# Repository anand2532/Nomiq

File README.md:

# Nomiq — Standalone LoRa Voice, Text & Photo Messenger

Nomiq is a pocket-sized, battery-powered messenger that sends **voice notes, offline speech-to-text messages and photographs** directly between devices over **LoRa** — no phone, no internet, no cellular, no cloud.

| | |
|---|---|
| **Main MCU** | ESP32-S3 (16 MB flash / 8 MB PSRAM) |
| **Radio** | Semtech SX1262, 865–867 MHz (India), 125 kHz BW |
| **Speech-to-text** | Offline — power-gated Linux co-processor (see [ADR-0002](docs/adr/0002-offline-speech-recognition-architecture.md)) |
| **Audio** | I²S MEMS mic, I²S class-D amp + speaker, Codec2 1200/2400 bps |
| **Camera** | OV2640 (DVP), on-chip JPEG |
| **Display** | 2.4–2.8" SPI TFT, 320×240 |
| **Storage** | microSD |
| **Power** | 1S Li-ion 3000 mAh, USB-C charging, fuel gauge |
| **Enclosure** | ~130 × 70 × 30 mm, 3D-printed (build123d, parametric) |
| **EDA** | KiCad 9/10, 4-layer |

## Repository map

```
docs/                    Requirements, architecture, specs, ADRs, roadmap
  00-requirements.md       Traceable requirements (REQ-xxx) from the product brief
  01-system-architecture.md
  02-hardware-architecture.md   Block diagram, pin map, power tree
  03-development-roadmap.md     Phases, gates, deliverables
  specs/                   Protocol, link budget, power budget, STT, UI, storage
  adr/                     Architecture Decision Records
hardware/
  kicad/nomiq/             KiCad project (schematic + PCB)
  bom/                     BOM and component selection
  bringup/                 Board bring-up checklist
mechanical/
  enclosure/               Parametric enclosure (build123d)
  exports/                 Generated STEP / STL (CI artefacts)
firmware/                  ESP-IDF project; protocol core is host-testable C
tools/                     Calculators (LoRa airtime, power budget)
tests/                     Test plans and reports
.claude/agents/            Engineering agent "bots" (one per discipline)
.mcp.json                  MCP servers: KiCad + CAD
```

## Getting started

```bash
# LoRa airtime / transfer-time table (India-compliant presets)
python3 tools/lora_airtime.py --table

# Host unit tests for the protocol core (no hardware needed)
make -C firmware/components/nomiq_proto/test

# Build the enclosure (needs: pip install build123d)
python3 mechanical/enclosure/enclosure.py --out mechanical/exports
```

Working with Claude Code and the engineering agents: see [docs/ai-workflow.md](docs/ai-workflow.md).

## Status

Phase 0 — architecture & de-risking. Original brief: [project.txt](project.txt). See [docs/03-development-roadmap.md](docs/03-development-roadmap.md).

**Gating risks (must close before PCB freeze):**
1. Offline STT on target hardware (Phase 3 benchmark) — ESP32-S3 alone cannot do free-form dictation.
2. Indian regulatory profile (duty-cycle / ERP) — drives photo/voice transfer times. See [lora-link-budget](docs/specs/lora-link-budget.md).
3. ESP32-S3 GPIO budget with camera + display + LoRa + SD + I²S — see pin map.

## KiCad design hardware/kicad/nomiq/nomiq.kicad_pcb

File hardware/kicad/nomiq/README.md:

# KiCad project — Nomiq main board

Open `nomiq.kicad_pro` in KiCad 8 or newer. The schematic is **generated** from the netlist source of truth
`hardware/design/nomiq_hw.py` by `hardware/design/gen_kicad.py`:

```
python3 hardware/design/gen_kicad.py          # regenerate nomiq.kicad_sch, 01..08 sheets, lib/nomiq.kicad_sym
python3 hardware/design/gen_kicad.py --check  # rebuild connectivity from the generated S-expressions and compare with nomiq_hw.py (runs in make tools / CI)
kicad-cli sch erc nomiq.kicad_sch             # ERC on a machine with KiCad
```

Structure: root sheet with 8 hierarchical sheets (power, MCU, radio, audio, camera, display+storage, UI, STT).
Every pin is connected by a short wire to a global label carrying the net name, so connectivity is exact and
the sheets are readable; unused pins carry no-connect flags. Edit `nomiq_hw.py`, not the `.kicad_sch` files.

Pad numbers: U1 (ESP32-S3-WROOM-1) and U2 (SX1262 QFN-24) follow the datasheets. 32 parts still use
placeholder pad numbers (marked `unverified` in `gen_kicad.py`) — verify against datasheets and assign
footprints before PCB layout (electronics-schematic-engineer, gate G2).

- Project libraries: `lib/nomiq.kicad_sym` (generated), `lib/nomiq.pretty` (registered in sym-lib-table / fp-lib-table)
- PCB: create `nomiq.kicad_pcb` from the PCB editor (Update PCB from schematic); outline from `mechanical/enclosure/params.py`
- Fabrication outputs: `fab/` (Gerbers, drill, CPL, BOM) — release via tag `hw-vX.Y`
- MCP: `.mcp.json` points kicad-mcp-pro at this folder (`KICAD_MCP_PROJECT_DIR`)

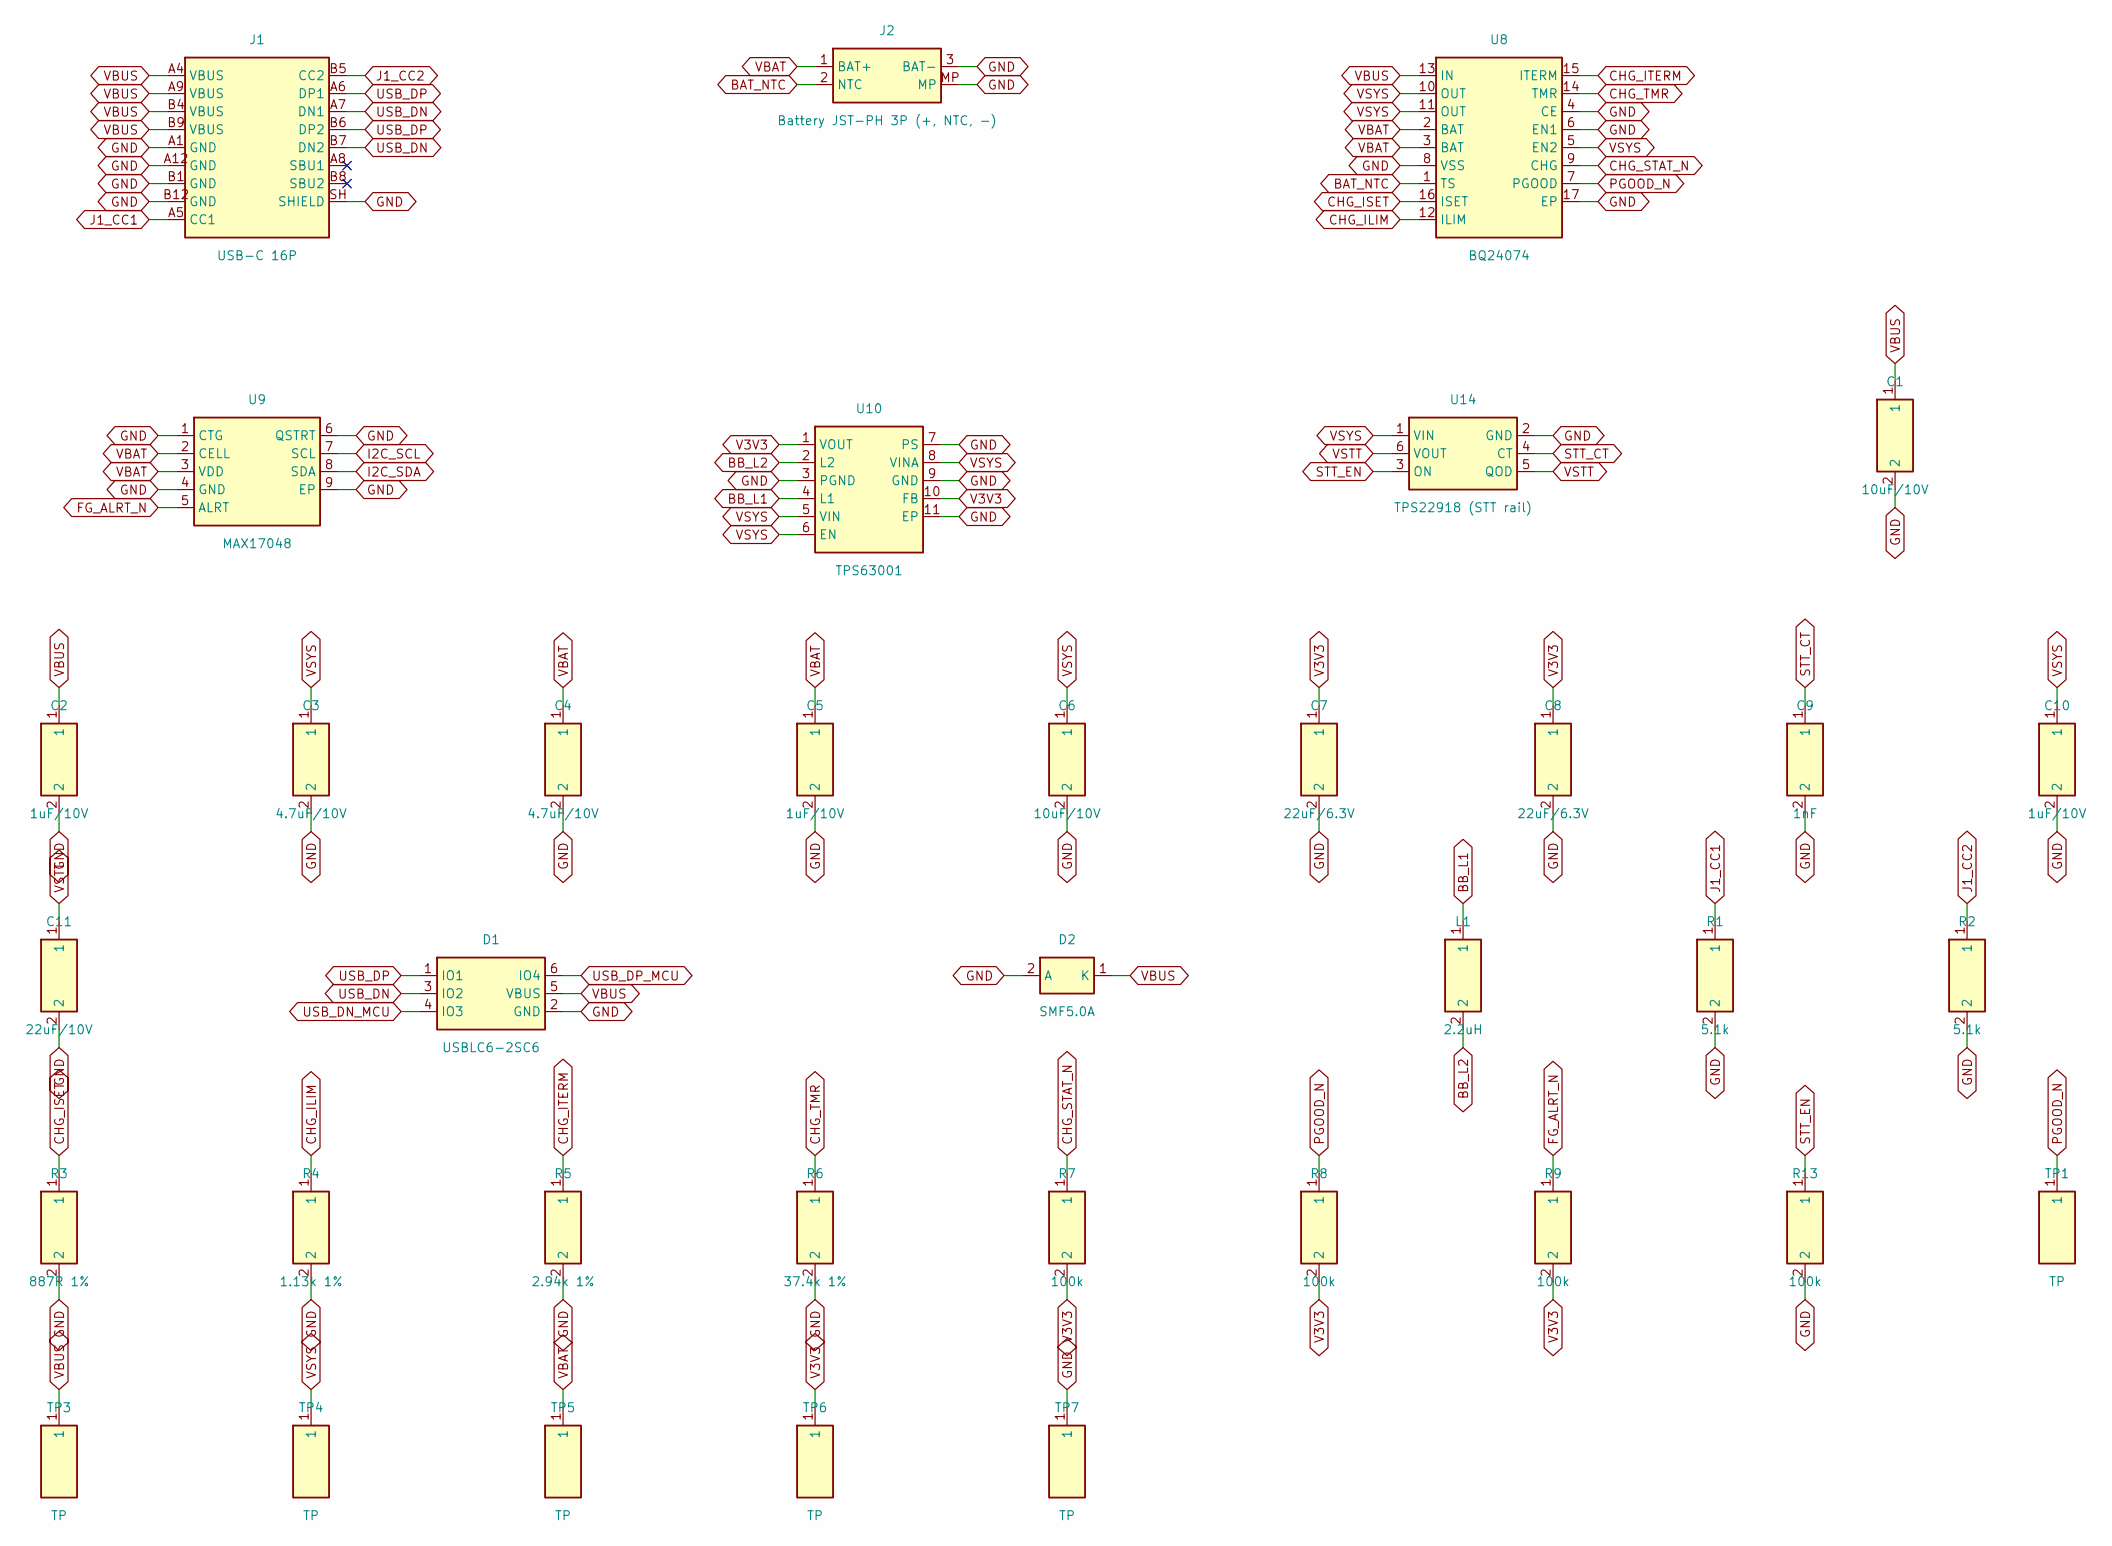
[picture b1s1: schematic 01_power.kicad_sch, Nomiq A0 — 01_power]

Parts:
C1, C6: 10uF/10V; C_0603_1608Metric
C2, C5, C10: 1uF/10V; C_0402_1005Metric
C3, C4: 4.7uF/10V; C_0603_1608Metric
C7, C8: 22uF/6.3V; C_0805_2012Metric
C9: 1nF; C_0402_1005Metric
C11: 22uF/10V; C_0805_2012Metric
D1: USBLC6-2SC6; SOT-23-6; MPN STMicro USBLC6-2SC6
D2: SMF5.0A; D_SOD-123F; MPN Littelfuse SMF5.0A
J1: USB-C 16P; USB_C_Receptacle_GCT_USB4105-xx-A_16P_TopMnt_Horizontal; MPN GCT USB4105-GF-A
J2: Battery JST-PH 3P (+, NTC, -); JST_PH_S3B-PH-SM4-TB_1x03-1MP_P2.00mm_Horizontal; MPN JST S3B-PH-SM4-TB
L1: 2.2uH; L_Taiyo-Yuden_NR-40xx; MPN Taiyo Yuden NRS4018T2R2MDGJ
R1, R2: 5.1k; R_0402_1005Metric
R3: 887R 1%; R_0402_1005Metric
R4: 1.13k 1%; R_0402_1005Metric
R5: 2.94k 1%; R_0402_1005Metric
R6: 37.4k 1%; R_0402_1005Metric
R7, R8, R9, R13: 100k; R_0402_1005Metric
TP1, TP3, TP4, TP5, TP6, TP7: TP; TestPoint_Pad_D1.0mm
U8: BQ24074; VQFN-16-1EP_3x3mm_P0.5mm_EP1.6x1.6mm; MPN TI BQ24074RGTR
U9: MAX17048; TDFN-8-1EP_2x2mm_P0.5mm_EP0.8x1.2mm; MPN Analog Devices MAX17048G+T10
U10: TPS63001; Texas_S-PVSON-N10; MPN TI TPS63001DRCR
U14: TPS22918 (STT rail); SOT-23-6; MPN TI TPS22918DBVR

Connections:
BAT_NTC: J2.2 (NTC), U8.1 (TS)
BB_L1: L1.1, U10.4 (L1)
BB_L2: L1.2, U10.2 (L2)
CHG_ILIM: R4.1, U8.12 (ILIM)
CHG_ISET: R3.1, U8.16 (ISET)
CHG_ITERM: R5.1, U8.15 (ITERM)
CHG_STAT_N: R7.1, U8.9 (CHG); also elsewhere on the board
CHG_TMR: R6.1, U8.14 (TMR)
FG_ALRT_N: R9.1, U9.5 (ALRT); also elsewhere on the board
GND: C1.2, C2.2, C3.2, C4.2, C5.2, C6.2, C7.2, C8.2, C9.2, C10.2, C11.2, D1.2 (GND), D2.2 (A), J1.A1 (GND), J1.A12 (GND), J1.B1 (GND), J1.B12 (GND), J1.SH (SHIELD), J2.3 (BAT-), J2.MP, R1.2, R2.2, R3.2, R4.2, R5.2, R6.2, R13.2, TP7.1, U8.4 (CE), U8.6 (EN1), U8.8 (VSS), U8.17 (EP), U9.1 (CTG), U9.4 (GND), U9.6 (QSTRT), U9.9 (EP), U10.3 (PGND), U10.7 (PS), U10.9 (GND), U10.11 (EP), U14.2 (GND); also elsewhere on the board
I2C_SCL: U9.7 (SCL); also elsewhere on the board
I2C_SDA: U9.8 (SDA); also elsewhere on the board
J1_CC1: J1.A5 (CC1), R1.1
J1_CC2: J1.B5 (CC2), R2.1
PGOOD_N: R8.1, TP1.1, U8.7 (PGOOD)
STT_CT: C9.1, U14.4 (CT)
STT_EN: R13.1, U14.3 (ON); also elsewhere on the board
USB_DN: D1.3 (IO2), J1.A7 (DN1), J1.B7 (DN2)
USB_DN_MCU: D1.4 (IO3); also elsewhere on the board
USB_DP: D1.1 (IO1), J1.A6 (DP1), J1.B6 (DP2)
USB_DP_MCU: D1.6 (IO4); also elsewhere on the board
V3V3: C7.1, C8.1, R7.2, R8.2, R9.2, TP6.1, U10.1 (VOUT), U10.10 (FB); also elsewhere on the board
VBAT: C4.1, C5.1, J2.1 (BAT+), TP5.1, U8.2 (BAT), U8.3 (BAT), U9.2 (CELL), U9.3 (VDD)
VBUS: C1.1, C2.1, D1.5 (VBUS), D2.1 (K), J1.A4 (VBUS), J1.A9 (VBUS), J1.B4 (VBUS), J1.B9 (VBUS), TP3.1, U8.13 (IN)
VSTT: C11.1, U14.5 (QOD), U14.6 (VOUT); also elsewhere on the board
VSYS: C3.1, C6.1, C10.1, TP4.1, U8.5 (EN2), U8.10 (OUT), U8.11 (OUT), U10.5 (VIN), U10.6 (EN), U10.8 (VINA), U14.1 (VIN); also elsewhere on the board

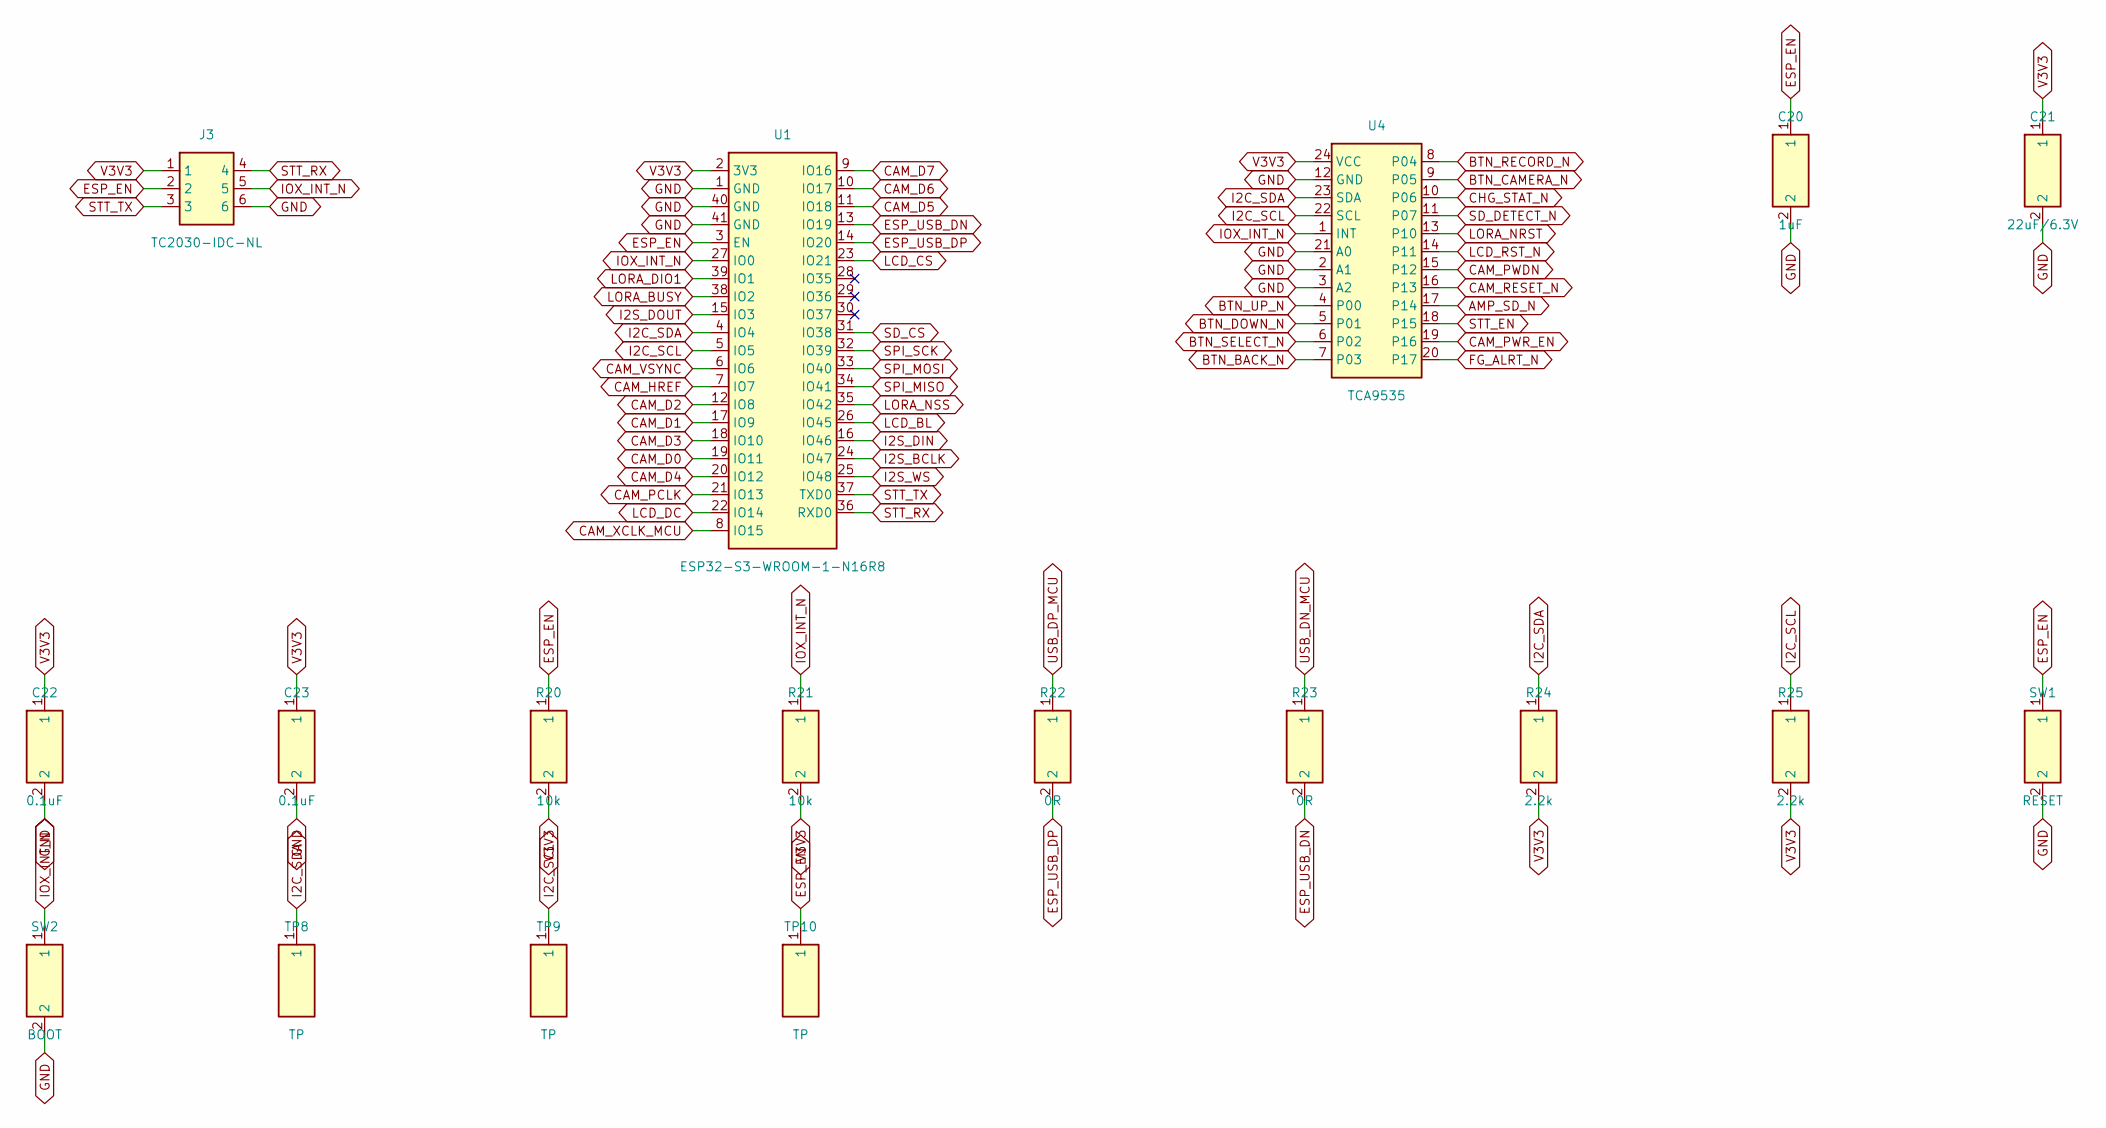
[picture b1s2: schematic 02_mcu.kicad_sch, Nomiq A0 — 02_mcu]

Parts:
C20: 1uF; C_0402_1005Metric
C21: 22uF/6.3V; C_0805_2012Metric
C22, C23: 0.1uF; C_0402_1005Metric
J3: TC2030-IDC-NL; Tag-Connect_TC2030-IDC-NL_2x03_P1.27mm_Vertical; MPN Tag-Connect TC2030-IDC-NL
R20, R21: 10k; R_0402_1005Metric
R22, R23: 0R; R_0402_1005Metric
R24, R25: 2.2k; R_0402_1005Metric
SW1: RESET; SW_SPST_PTS810; MPN C&K PTS810 SJM 250 SMTR LFS
SW2: BOOT; SW_SPST_PTS810; MPN C&K PTS810 SJM 250 SMTR LFS
TP8, TP9, TP10: TP; TestPoint_Pad_D1.0mm
U1: ESP32-S3-WROOM-1-N16R8; ESP32-S3-WROOM-1; MPN Espressif ESP32-S3-WROOM-1-N16R8
U4: TCA9535; TSSOP-24_4.4x7.8mm_P0.65mm; MPN TI TCA9535PWR

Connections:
AMP_SD_N: U4.17 (P14); also elsewhere on the board
BTN_BACK_N: U4.7 (P03); also elsewhere on the board
BTN_CAMERA_N: U4.9 (P05); also elsewhere on the board
BTN_DOWN_N: U4.5 (P01); also elsewhere on the board
BTN_RECORD_N: U4.8 (P04); also elsewhere on the board
BTN_SELECT_N: U4.6 (P02); also elsewhere on the board
BTN_UP_N: U4.4 (P00); also elsewhere on the board
CAM_D0: U1.19 (IO11); also elsewhere on the board
CAM_D1: U1.17 (IO9); also elsewhere on the board
CAM_D2: U1.12 (IO8); also elsewhere on the board
CAM_D3: U1.18 (IO10); also elsewhere on the board
CAM_D4: U1.20 (IO12); also elsewhere on the board
CAM_D5: U1.11 (IO18); also elsewhere on the board
CAM_D6: U1.10 (IO17); also elsewhere on the board
CAM_D7: U1.9 (IO16); also elsewhere on the board
CAM_HREF: U1.7 (IO7); also elsewhere on the board
CAM_PCLK: U1.21 (IO13); also elsewhere on the board
CAM_PWDN: U4.15 (P12); also elsewhere on the board
CAM_PWR_EN: U4.19 (P16); also elsewhere on the board
CAM_RESET_N: U4.16 (P13); also elsewhere on the board
CAM_VSYNC: U1.6 (IO6); also elsewhere on the board
CAM_XCLK_MCU: U1.8 (IO15); also elsewhere on the board
CHG_STAT_N: U4.10 (P06); also elsewhere on the board
ESP_EN: C20.1, J3.2, R20.1, SW1.1, TP10.1, U1.3 (EN); also elsewhere on the board
ESP_USB_DN: R23.2, U1.13 (IO19)
ESP_USB_DP: R22.2, U1.14 (IO20)
FG_ALRT_N: U4.20 (P17); also elsewhere on the board
GND: C20.2, C21.2, C22.2, C23.2, J3.6, SW1.2, SW2.2, U1.1 (GND), U1.40 (GND), U1.41 (GND), U4.2 (A1), U4.3 (A2), U4.12 (GND), U4.21 (A0); also elsewhere on the board
I2C_SCL: R25.1, TP9.1, U1.5 (IO5), U4.22 (SCL); also elsewhere on the board
I2C_SDA: R24.1, TP8.1, U1.4 (IO4), U4.23 (SDA); also elsewhere on the board
I2S_BCLK: U1.24 (IO47); also elsewhere on the board
I2S_DIN: U1.16 (IO46); also elsewhere on the board
I2S_DOUT: U1.15 (IO3); also elsewhere on the board
I2S_WS: U1.25 (IO48); also elsewhere on the board
IOX_INT_N: J3.5, R21.1, SW2.1, U1.27 (IO0), U4.1 (INT)
LCD_BL: U1.26 (IO45); also elsewhere on the board
LCD_CS: U1.23 (IO21); also elsewhere on the board
LCD_DC: U1.22 (IO14); also elsewhere on the board
LCD_RST_N: U4.14 (P11); also elsewhere on the board
LORA_BUSY: U1.38 (IO2); also elsewhere on the board
LORA_DIO1: U1.39 (IO1); also elsewhere on the board
LORA_NRST: U4.13 (P10); also elsewhere on the board
LORA_NSS: U1.35 (IO42); also elsewhere on the board
SD_CS: U1.31 (IO38); also elsewhere on the board
SD_DETECT_N: U4.11 (P07); also elsewhere on the board
SPI_MISO: U1.34 (IO41); also elsewhere on the board
SPI_MOSI: U1.33 (IO40); also elsewhere on the board
SPI_SCK: U1.32 (IO39); also elsewhere on the board
STT_EN: U4.18 (P15); also elsewhere on the board
STT_RX: J3.4, U1.36 (RXD0); also elsewhere on the board
STT_TX: J3.3, U1.37 (TXD0); also elsewhere on the board
USB_DN_MCU: R23.1; also elsewhere on the board
USB_DP_MCU: R22.1; also elsewhere on the board
V3V3: C21.1, C22.1, C23.1, J3.1, R20.2, R21.2, R24.2, R25.2, U1.2 (3V3), U4.24 (VCC); also elsewhere on the board

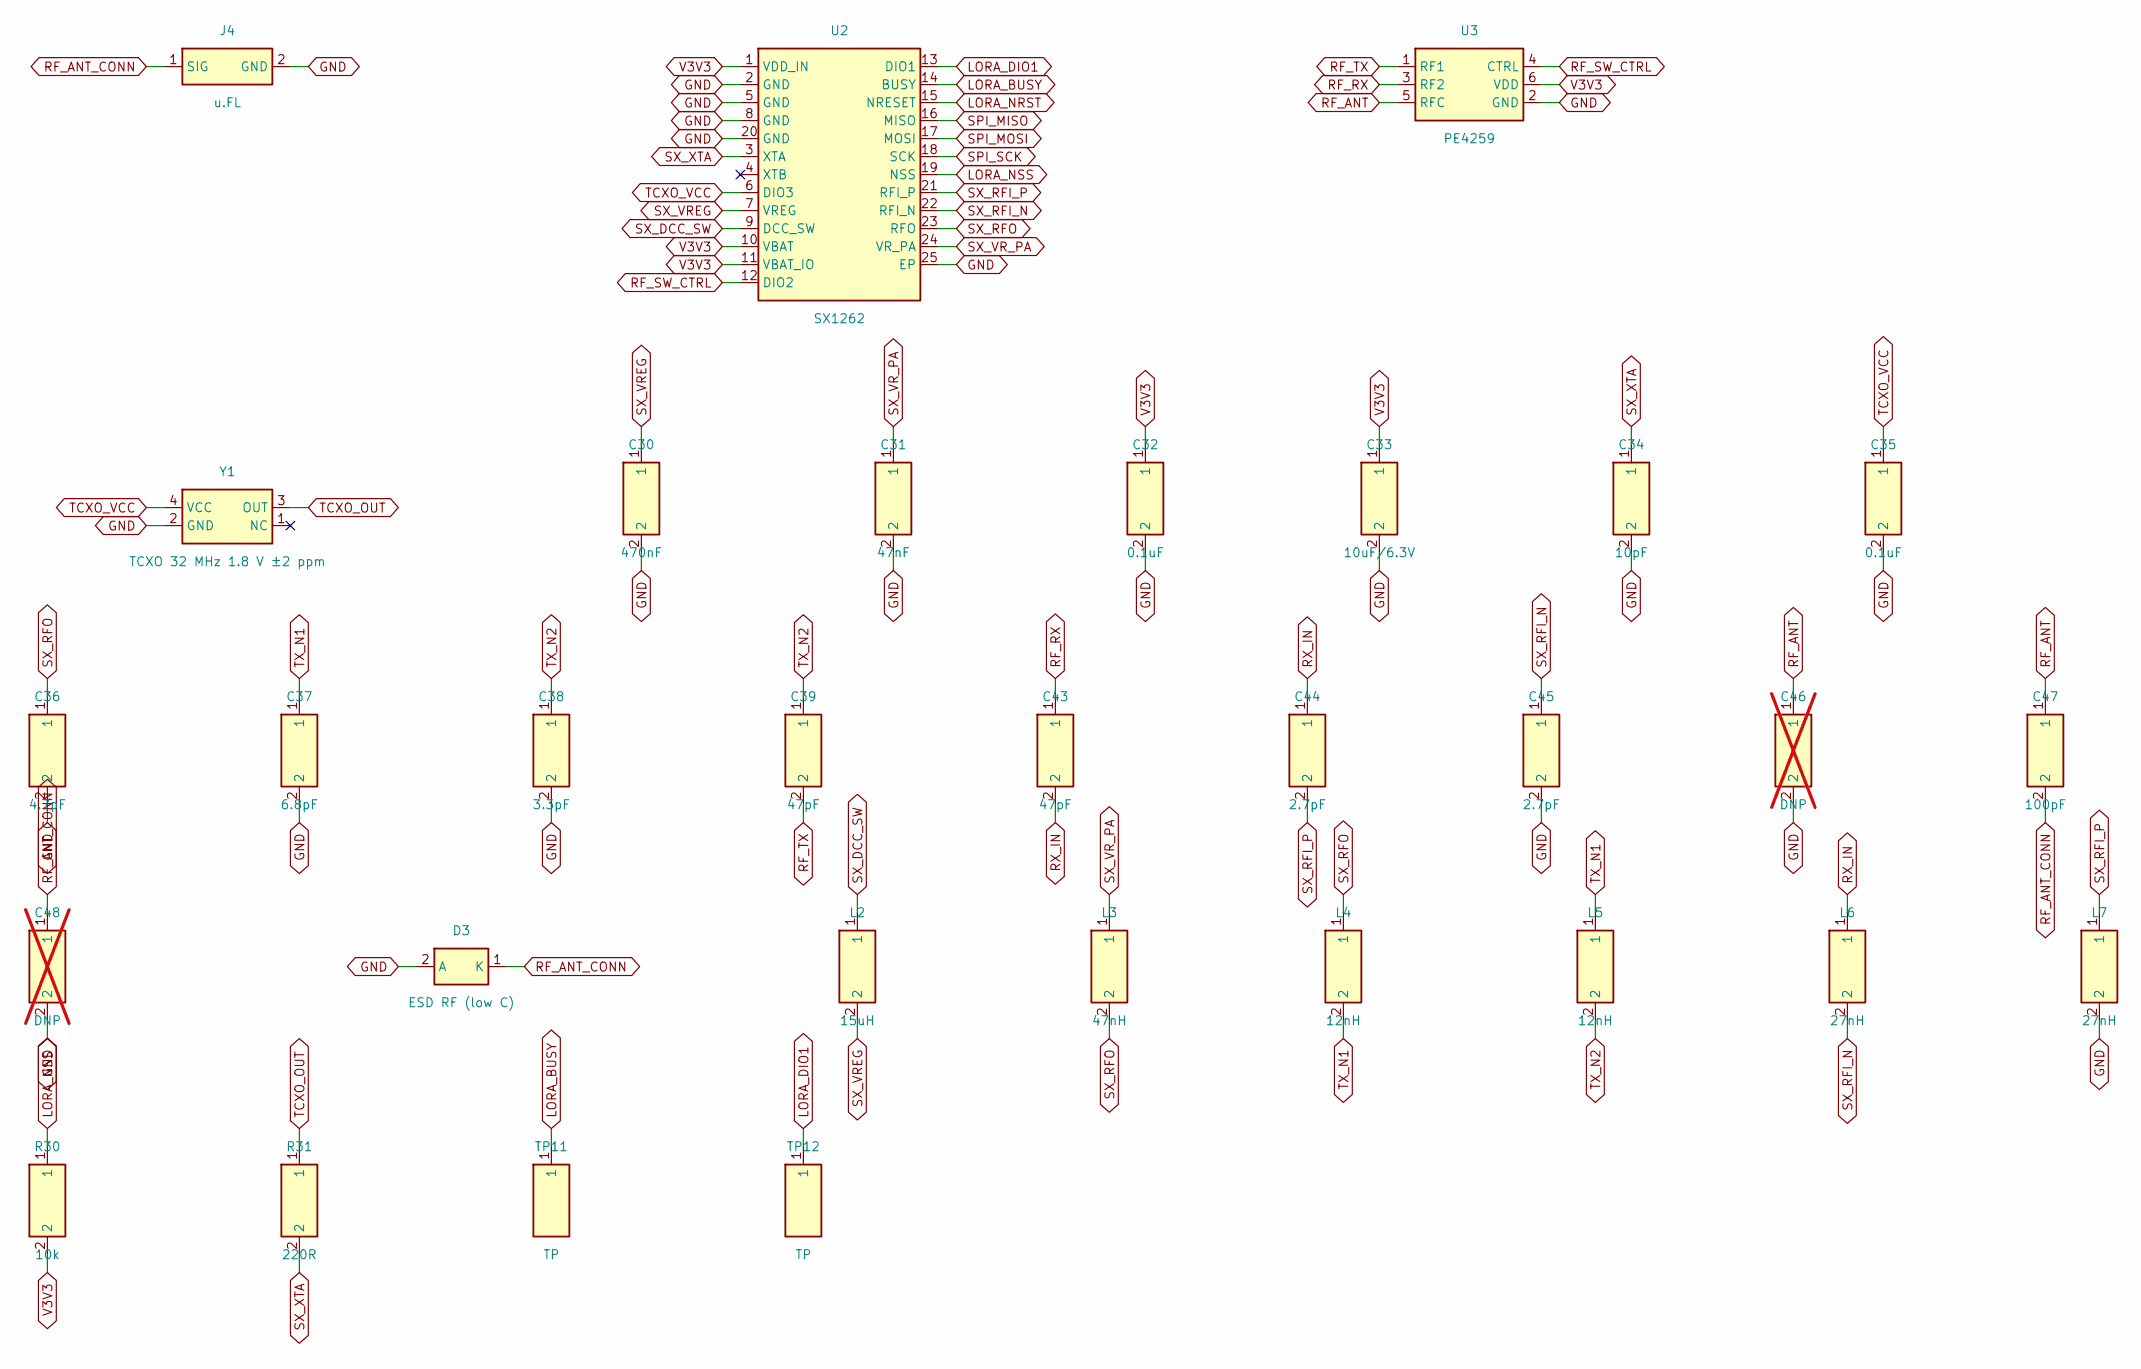
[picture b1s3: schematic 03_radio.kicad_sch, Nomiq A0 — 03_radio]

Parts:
C30: 470nF; C_0402_1005Metric
C31: 47nF; C_0402_1005Metric
C32, C35: 0.1uF; C_0402_1005Metric
C33: 10uF/6.3V; C_0603_1608Metric
C34: 10pF; C_0402_1005Metric
C36: 4.7pF; C_0402_1005Metric
C37: 6.8pF; C_0402_1005Metric
C38: 3.3pF; C_0402_1005Metric
C39, C43: 47pF; C_0402_1005Metric
C44, C45: 2.7pF; C_0402_1005Metric
C46, C48: DNP; C_0402_1005Metric; not fitted
C47: 100pF; C_0402_1005Metric
D3: ESD RF (low C); D_0201_0603Metric; MPN Infineon ESD0P2RF-02LS
J4: u.FL; U.FL_Hirose_U.FL-R-SMT-1_Vertical; MPN Hirose U.FL-R-SMT-1(10)
L2: 15uH; L_0805_2012Metric; MPN Murata LQM21FN150M70L
L3: 47nH; L_0402_1005Metric; MPN Murata LQW15AN47NJ00
L4, L5: 12nH; L_0402_1005Metric; MPN Murata LQW15AN12NJ00
L6, L7: 27nH; L_0402_1005Metric; MPN Murata LQW15AN27NJ00
R30: 10k; R_0402_1005Metric
R31: 220R; R_0402_1005Metric
TP11, TP12: TP; TestPoint_Pad_D1.0mm
U2: SX1262; QFN-24-1EP_4x4mm_P0.5mm_EP2.6x2.6mm; MPN Semtech SX1262IMLTRT
U3: PE4259; SOT-363_SC-70-6; MPN pSemi PE4259-63
Y1: TCXO 32 MHz 1.8 V ±2 ppm; Crystal_SMD_2016-4Pin_2.0x1.6mm; MPN Epson TG2016SMN 32.0000M-ECGNNM3

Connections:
GND: C30.2, C31.2, C32.2, C33.2, C34.2, C35.2, C36.2, C37.2, C38.2, C45.2, C46.2, C48.2, D3.2 (A), J4.2 (GND), L7.2, U2.2 (GND), U2.5 (GND), U2.8 (GND), U2.20 (GND), U2.25 (EP), U3.2 (GND), Y1.2 (GND); also elsewhere on the board
LORA_BUSY: TP11.1, U2.14 (BUSY); also elsewhere on the board
LORA_DIO1: TP12.1, U2.13 (DIO1); also elsewhere on the board
LORA_NRST: U2.15 (NRESET); also elsewhere on the board
LORA_NSS: R30.1, U2.19 (NSS); also elsewhere on the board
RF_ANT: C46.1, C47.1, U3.5 (RFC)
RF_ANT_CONN: C47.2, C48.1, D3.1 (K), J4.1 (SIG)
RF_RX: C43.1, U3.3 (RF2)
RF_SW_CTRL: U2.12 (DIO2), U3.4 (CTRL)
RF_TX: C39.2, U3.1 (RF1)
RX_IN: C43.2, C44.1, L6.1
SPI_MISO: U2.16 (MISO); also elsewhere on the board
SPI_MOSI: U2.17 (MOSI); also elsewhere on the board
SPI_SCK: U2.18 (SCK); also elsewhere on the board
SX_DCC_SW: L2.1, U2.9 (DCC_SW)
SX_RFI_N: C45.1, L6.2, U2.22 (RFI_N)
SX_RFI_P: C44.2, L7.1, U2.21 (RFI_P)
SX_RFO: C36.1, L3.2, L4.1, U2.23 (RFO)
SX_VREG: C30.1, L2.2, U2.7 (VREG)
SX_VR_PA: C31.1, L3.1, U2.24 (VR_PA)
SX_XTA: C34.1, R31.2, U2.3 (XTA)
TCXO_OUT: R31.1, Y1.3 (OUT)
TCXO_VCC: C35.1, U2.6 (DIO3), Y1.4 (VCC)
TX_N1: C37.1, L4.2, L5.1
TX_N2: C38.1, C39.1, L5.2
V3V3: C32.1, C33.1, R30.2, U2.1 (VDD_IN), U2.10 (VBAT), U2.11 (VBAT_IO), U3.6 (VDD); also elsewhere on the board

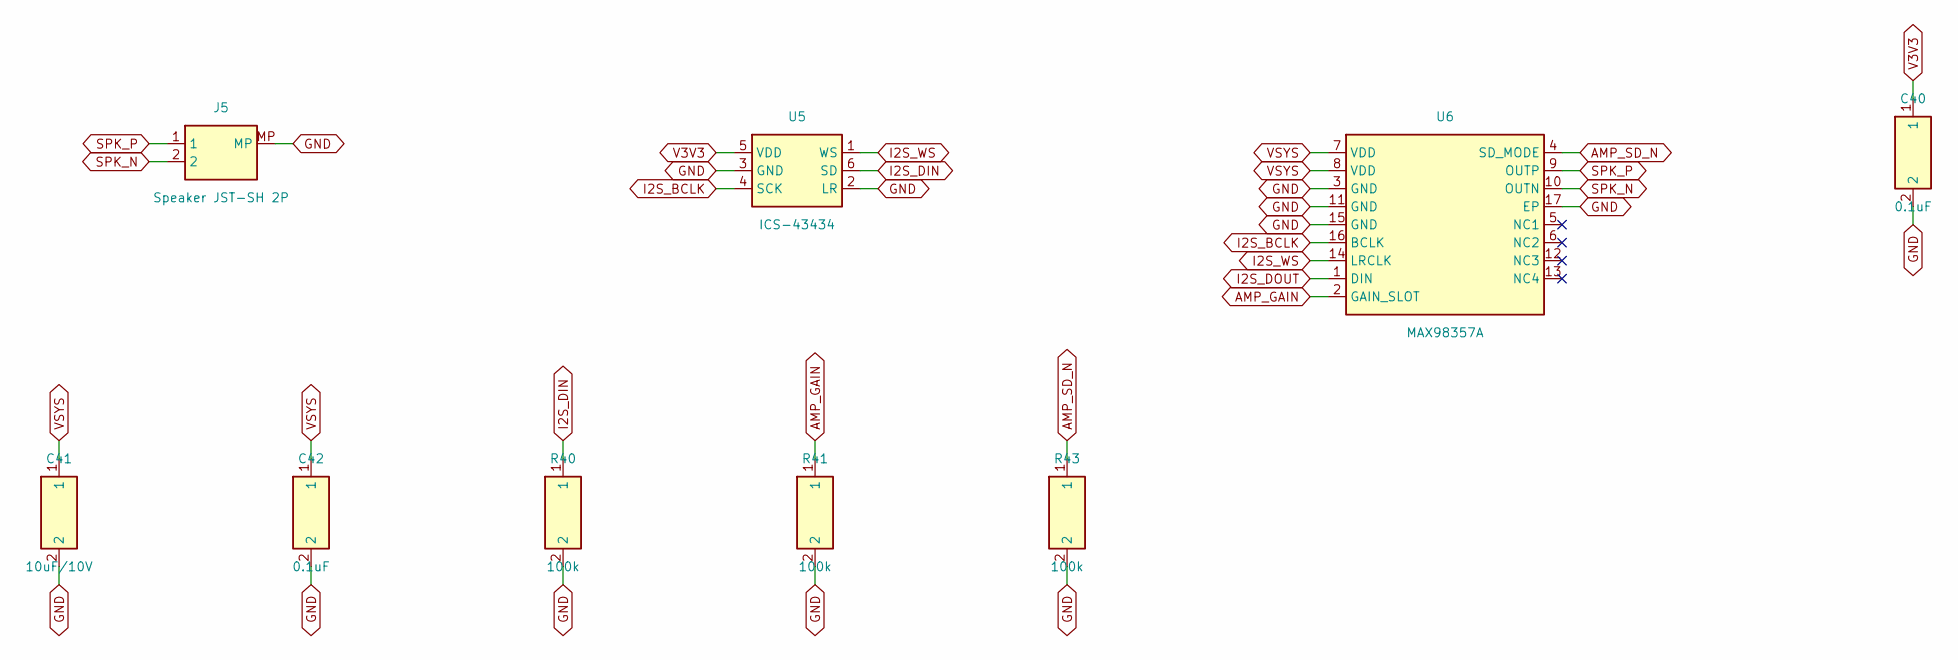
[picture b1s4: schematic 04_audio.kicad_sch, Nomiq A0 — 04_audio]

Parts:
C40, C42: 0.1uF; C_0402_1005Metric
C41: 10uF/10V; C_0603_1608Metric
J5: Speaker JST-SH 2P; JST_SH_SM02B-SRSS-TB_1x02-1MP_P1.00mm_Horizontal; MPN JST SM02B-SRSS-TB
R40, R41, R43: 100k; R_0402_1005Metric
U5: ICS-43434; InvenSense_ICS-43434-6_3.5x2.65mm; MPN TDK InvenSense ICS-43434
U6: MAX98357A; TQFN-16-1EP_3x3mm_P0.5mm_EP1.23x1.23mm; MPN Analog Devices MAX98357AETE+T

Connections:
AMP_GAIN: R41.1, U6.2 (GAIN_SLOT)
AMP_SD_N: R43.1, U6.4 (SD_MODE); also elsewhere on the board
GND: C40.2, C41.2, C42.2, J5.MP, R40.2, R41.2, R43.2, U5.2 (LR), U5.3 (GND), U6.3 (GND), U6.11 (GND), U6.15 (GND), U6.17 (EP); also elsewhere on the board
I2S_BCLK: U5.4 (SCK), U6.16 (BCLK); also elsewhere on the board
I2S_DIN: R40.1, U5.6 (SD); also elsewhere on the board
I2S_DOUT: U6.1 (DIN); also elsewhere on the board
I2S_WS: U5.1 (WS), U6.14 (LRCLK); also elsewhere on the board
SPK_N: J5.2, U6.10 (OUTN)
SPK_P: J5.1, U6.9 (OUTP)
V3V3: C40.1, U5.5 (VDD); also elsewhere on the board
VSYS: C41.1, C42.1, U6.7 (VDD), U6.8 (VDD); also elsewhere on the board

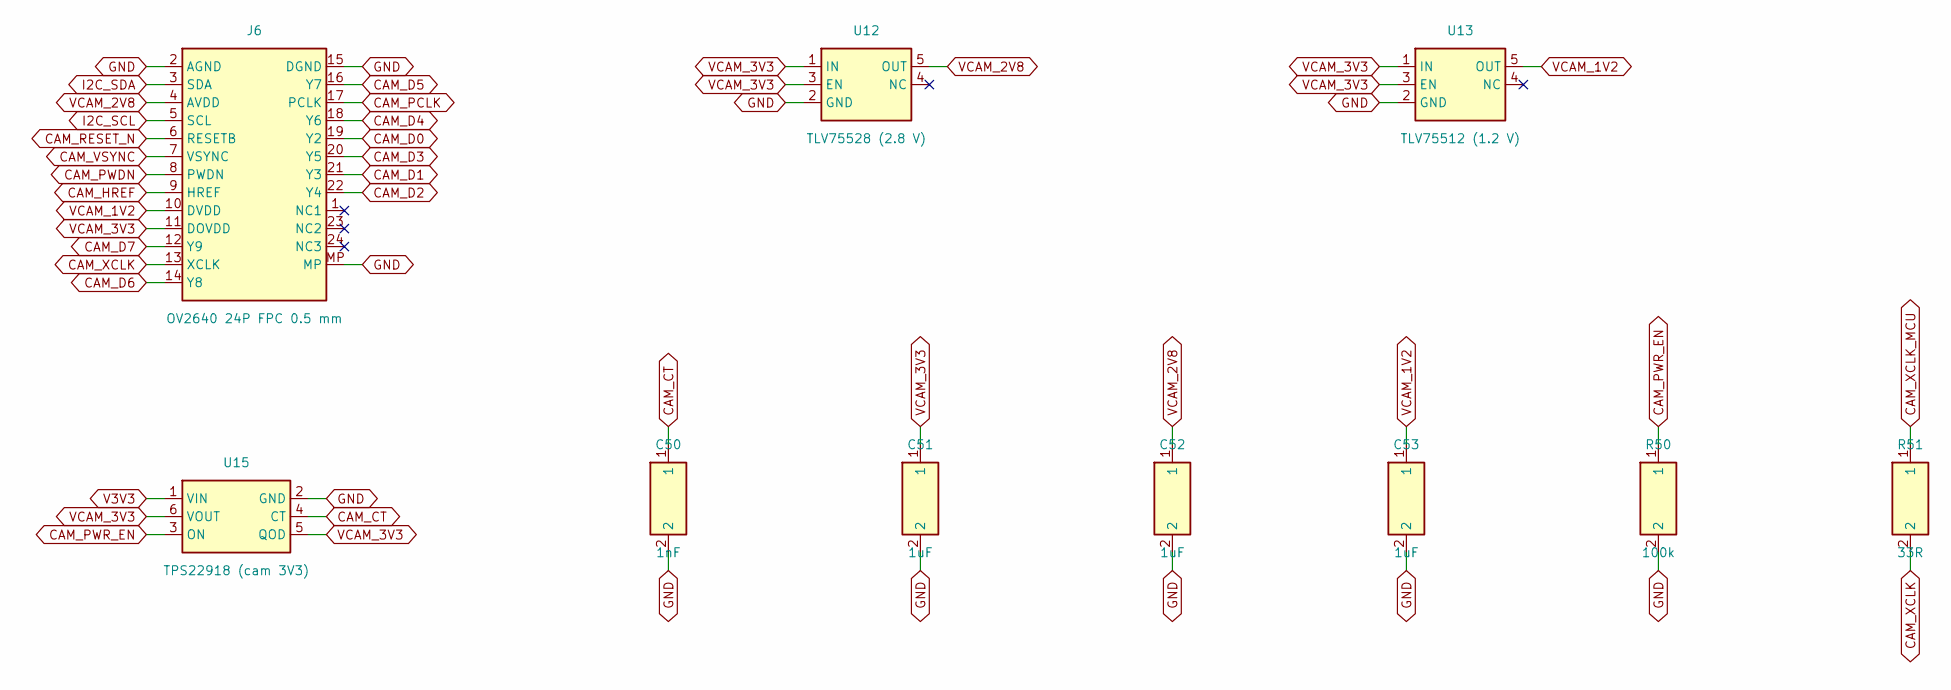
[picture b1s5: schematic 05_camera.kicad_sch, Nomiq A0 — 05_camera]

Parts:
C50: 1nF; C_0402_1005Metric
C51, C52, C53: 1uF; C_0402_1005Metric
J6: OV2640 24P FPC 0.5 mm; Hirose_FH12-24S-0.5SH_1x24-1MP_P0.50mm_Horizontal; MPN Hirose FH12-24S-0.5SH(55)
R50: 100k; R_0402_1005Metric
R51: 33R; R_0402_1005Metric
U12: TLV75528 (2.8 V); SOT-23-5; MPN TI TLV75528PDBVR
U13: TLV75512 (1.2 V); SOT-23-5; MPN TI TLV75512PDBVR
U15: TPS22918 (cam 3V3); SOT-23-6; MPN TI TPS22918DBVR

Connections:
CAM_CT: C50.1, U15.4 (CT)
CAM_D0: J6.19 (Y2); also elsewhere on the board
CAM_D1: J6.21 (Y3); also elsewhere on the board
CAM_D2: J6.22 (Y4); also elsewhere on the board
CAM_D3: J6.20 (Y5); also elsewhere on the board
CAM_D4: J6.18 (Y6); also elsewhere on the board
CAM_D5: J6.16 (Y7); also elsewhere on the board
CAM_D6: J6.14 (Y8); also elsewhere on the board
CAM_D7: J6.12 (Y9); also elsewhere on the board
CAM_HREF: J6.9 (HREF); also elsewhere on the board
CAM_PCLK: J6.17 (PCLK); also elsewhere on the board
CAM_PWDN: J6.8 (PWDN); also elsewhere on the board
CAM_PWR_EN: R50.1, U15.3 (ON); also elsewhere on the board
CAM_RESET_N: J6.6 (RESETB); also elsewhere on the board
CAM_VSYNC: J6.7 (VSYNC); also elsewhere on the board
CAM_XCLK: J6.13 (XCLK), R51.2
CAM_XCLK_MCU: R51.1; also elsewhere on the board
GND: C50.2, C51.2, C52.2, C53.2, J6.2 (AGND), J6.15 (DGND), J6.MP, R50.2, U12.2 (GND), U13.2 (GND), U15.2 (GND); also elsewhere on the board
I2C_SCL: J6.5 (SCL); also elsewhere on the board
I2C_SDA: J6.3 (SDA); also elsewhere on the board
V3V3: U15.1 (VIN); also elsewhere on the board
VCAM_1V2: C53.1, J6.10 (DVDD), U13.5 (OUT)
VCAM_2V8: C52.1, J6.4 (AVDD), U12.5 (OUT)
VCAM_3V3: C51.1, J6.11 (DOVDD), U12.1 (IN), U12.3 (EN), U13.1 (IN), U13.3 (EN), U15.5 (QOD), U15.6 (VOUT)

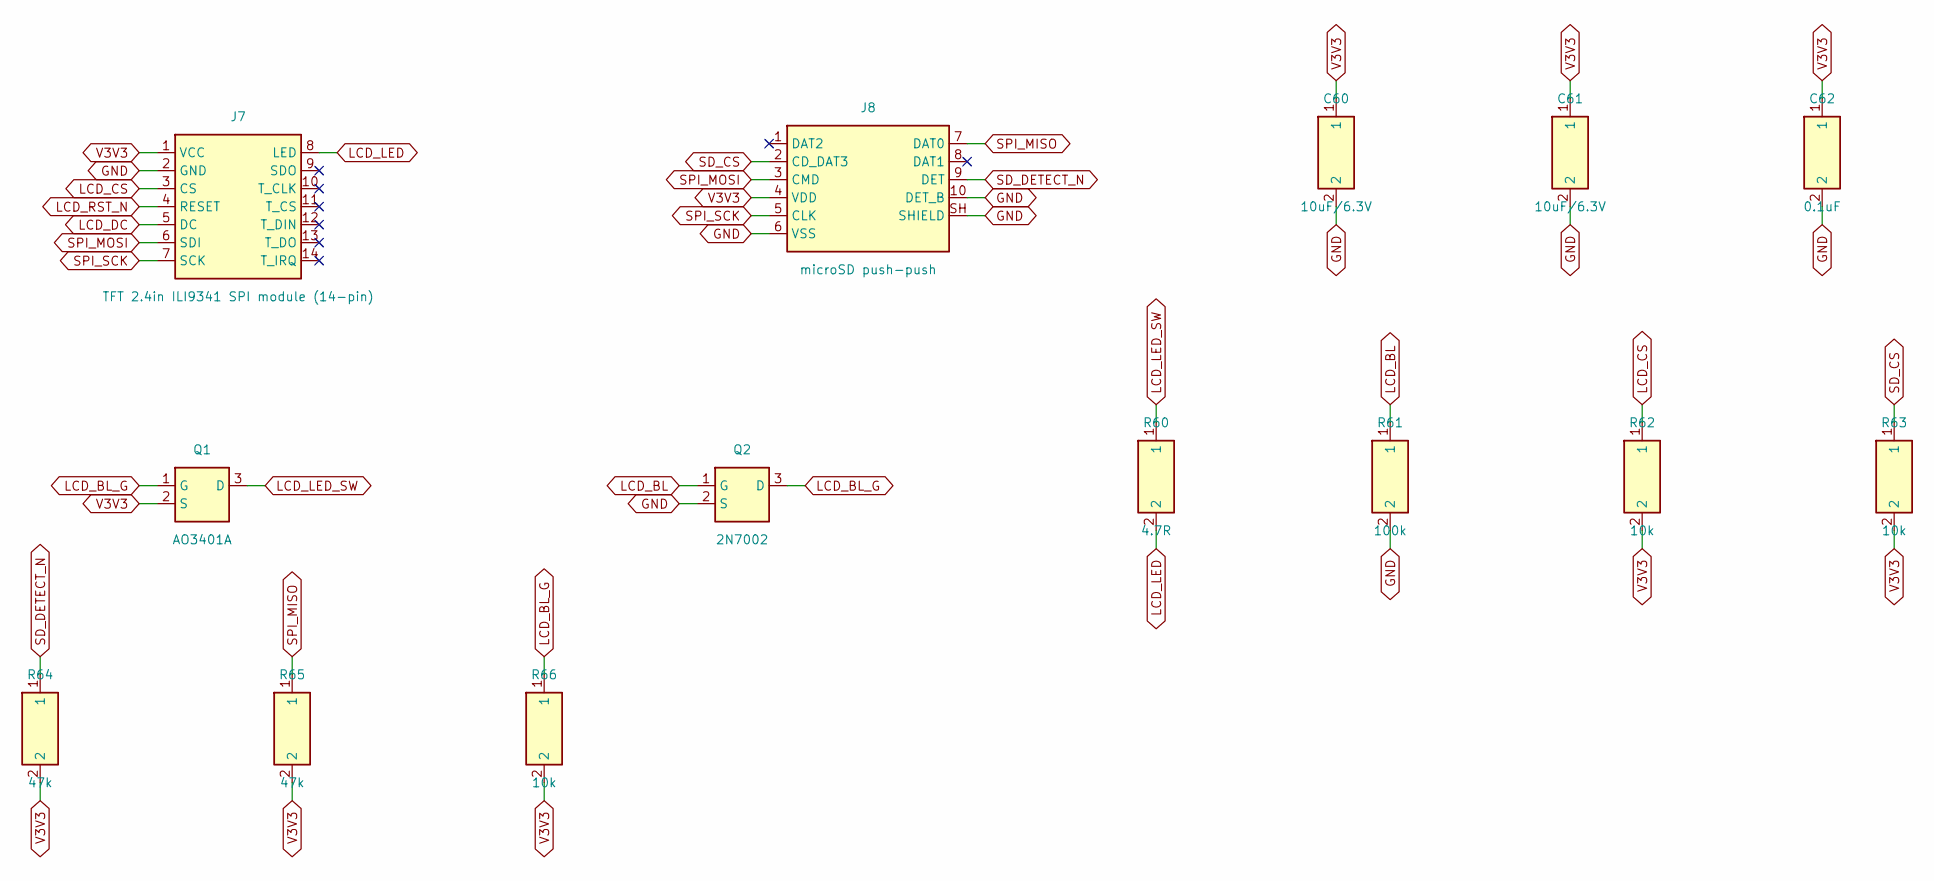
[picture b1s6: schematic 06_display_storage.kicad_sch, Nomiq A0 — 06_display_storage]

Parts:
C60, C61: 10uF/6.3V; C_0603_1608Metric
C62: 0.1uF; C_0402_1005Metric
J7: TFT 2.4in ILI9341 SPI module (14-pin); TFT_2.4in_ILI9341_1x14; MPN 2.4in 240x320 ILI9341 SPI module, 1x14 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
J8: microSD push-push; microSD_HC_Molex_104031-0811; MPN Molex 104031-0811
Q1: AO3401A; SOT-23; MPN AOS AO3401A
Q2: 2N7002; SOT-23; MPN Nexperia 2N7002,215
R60: 4.7R; R_0402_1005Metric
R61: 100k; R_0402_1005Metric
R62, R63, R66: 10k; R_0402_1005Metric
R64, R65: 47k; R_0402_1005Metric

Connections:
GND: C60.2, C61.2, C62.2, J7.2 (GND), J8.6 (VSS), J8.10 (DET_B), J8.SH (SHIELD), Q2.2 (S), R61.2; also elsewhere on the board
LCD_BL: Q2.1 (G), R61.1; also elsewhere on the board
LCD_BL_G: Q1.1 (G), Q2.3 (D), R66.1
LCD_CS: J7.3 (CS), R62.1; also elsewhere on the board
LCD_DC: J7.5 (DC); also elsewhere on the board
LCD_LED: J7.8 (LED), R60.2
LCD_LED_SW: Q1.3 (D), R60.1
LCD_RST_N: J7.4 (RESET); also elsewhere on the board
SD_CS: J8.2 (CD_DAT3), R63.1; also elsewhere on the board
SD_DETECT_N: J8.9 (DET), R64.1; also elsewhere on the board
SPI_MISO: J8.7 (DAT0), R65.1; also elsewhere on the board
SPI_MOSI: J7.6 (SDI), J8.3 (CMD); also elsewhere on the board
SPI_SCK: J7.7 (SCK), J8.5 (CLK); also elsewhere on the board
V3V3: C60.1, C61.1, C62.1, J7.1 (VCC), J8.4 (VDD), Q1.2 (S), R62.2, R63.2, R64.2, R65.2, R66.2; also elsewhere on the board
